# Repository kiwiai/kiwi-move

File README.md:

The Kiwi Move

These are the hardware design files for the Kiwi Move, developed by Kiwi Wearable Technologies Ltd.

These files have been made available online through a Creative Commons Attribution-ShareAlike 3.0 license. You are welcome to distribute, remix, and use these files for commercial purposes. If you do so, please attribute the original design to Kiwi Wearable Technologies Ltd. and all parties involved in developing to this point including Spark Devices in your schematic. All derivative works must be published under the same or a similar license. The design is built off of a number of open source projects including the Spark Core (https://github.com/spark/core)

Development of the Kiwi Move began in May 2013 in Toronto, Canada after the founding team participated in a local computer competition. The Kiwi Platform began its development in the spring of 2011 built on the basis of a number of sensorial and data acquisition devices. This initial release of hardware design files are for those in the GitHub and open-source community to make the most of for wearable technology devices.

What Hardware Design Files are Included:

EAGLE — Schematic and board files for the Kiwi Move. 

GERBER Files - For making your own runs of the Kiwi Move.

Pin Mapping — Detailed pin mapping of the Kiwi Move and STM32, providing information about which pins are mapped to which peripherals.

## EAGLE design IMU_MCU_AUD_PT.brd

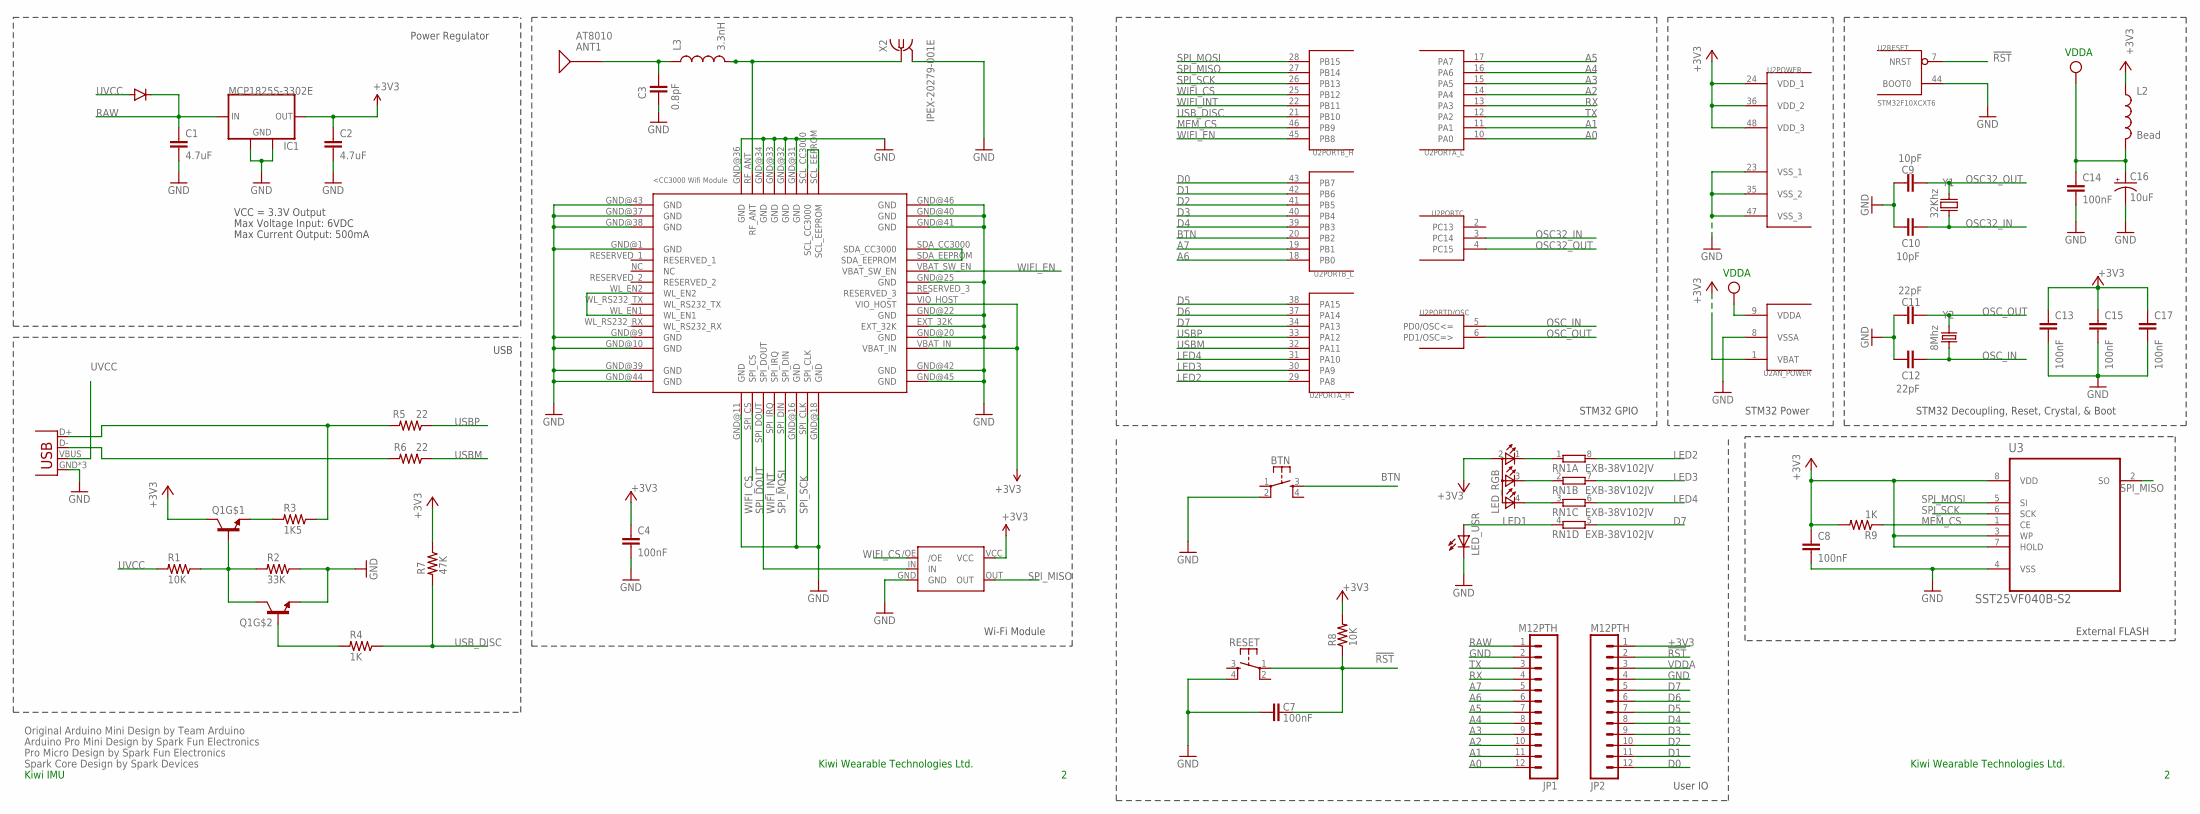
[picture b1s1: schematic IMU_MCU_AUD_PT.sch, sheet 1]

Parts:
ANT1: AT8010
B1: NL17SZ125SOT553; SOT-553
BTN: KMR211GLFS; TACTILE_SWITCH_SMD
C1, C2: 4.7uF; C0603
C3: 0.8pF; C0603
C4, C7, C8, C13, C14, C15, C17: 100nF; C0603
C9, C10: 10pF; C0603
C11, C12: 22pF; C0603
C16: 10uF; EIA3216
IC1: MCP1825S-3302E; SOT223
JP1, JP2: M12PTH; 1X12-SMALL-PADS
L2: Bead; 0603
L3: 3.3nH; 0603
LED_RGB: TOPLED-3PLCC; P-LCC-4-3
LED_USR: LED0603; LED-0603
Q1: MMDT3904; SOT363
R1, R8: 10K; R0603
R2: 33K; R0603
R3: 1K5; R0603
R4, R9: 1K; R0603
R5, R6: 22; R0603
R7: 47K; R0603
RESET: KMR211GLFS; TACTILE_SWITCH_SMD
RN1: EXB-38V102JV; EXB38V
U1: CC3000
U2: STM32F10XCXT6; TQFP48
U3: SST25VF040B-S2; SOIC127P790X216-8N
U$3: DIODE; DIODE-DO-220AA(SMP)
X1: USB-MICROB; USB-MICROB-SLOT-HOLE
X2: IPEX-20279-001E
Y1: 32Khz; FC135
Y2: 8Mhz; CRYSTAL-SMD-5X3

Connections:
3.3V: B1.VCC
!RST: C7.2, JP2.2, R8.1, RESET.1, U2.7 (NRST)
+3V3: C2.1, C4.1, C8.1, C13.1, C15.1, C17.1, IC1.3 (OUT), JP2.1, L2.1, LED_RGB.2 (A2), Q1.3 (C), R7.1, R8.2, R9.2, U1.VBAT_IN, U1.VIO_HOST, U2.1 (VBAT), U2.24 (VDD_1), U2.36 (VDD_2), U2.48 (VDD_3), U3.3 (WP), U3.7 (HOLD), U3.8 (VDD); also elsewhere on the board
A0: JP1.12, U2.10 (PA0); also elsewhere on the board
A1: JP1.11, U2.11 (PA1); also elsewhere on the board
A2: JP1.10, U2.14 (PA4)
A3: JP1.9, U2.15 (PA5)
A4: JP1.8, U2.16 (PA6)
A5: JP1.7, U2.17 (PA7)
A6: JP1.6, U2.18 (PB0); also elsewhere on the board
A7: JP1.5, U2.19 (PB1)
BTN: BTN.3, U2.20 (PB2)
D0: JP2.12, U2.43 (PB7); also elsewhere on the board
D1: JP2.11, U2.42 (PB6); also elsewhere on the board
D2: JP2.10, U2.41 (PB5)
D3: JP2.9, U2.40 (PB4); also elsewhere on the board
D4: JP2.8, U2.39 (PB3); also elsewhere on the board
D5: JP2.7, U2.38 (PA15); also elsewhere on the board
D6: JP2.6, U2.37 (PA14); also elsewhere on the board
D7: JP2.5, RN1.5 (2), U2.34 (PA13)
GND: B1.GND, BTN.2, C1.2, C2.2, C3.1, C4.2, C7.1, C8.2, C9.2, C10.2, C11.2, C12.2, C13.2, C14.2, C15.2, C16.C (-), C17.2, IC1.2 (GND), IC1.4 (GND), JP1.2, JP2.4, LED_USR.C, Q1.1 (E), R2.1, RESET.4, U1.EXT_32K, U1.GND@1 (GND), U1.GND@9 (GND), U1.GND@10 (GND), U1.GND@11 (GND), U1.GND@16 (GND), U1.GND@18 (GND), U1.GND@20 (GND), U1.GND@22 (GND), U1.GND@25 (GND), U1.GND@31 (GND), U1.GND@32 (GND), U1.GND@33 (GND), U1.GND@34 (GND), U1.GND@36 (GND), U1.GND@37 (GND), U1.GND@38 (GND), U1.GND@39 (GND), U1.GND@40 (GND), U1.GND@41 (GND), U1.GND@42 (GND), U1.GND@43 (GND), U1.GND@44 (GND), U1.GND@45 (GND), U1.GND@46 (GND), U2.8 (VSSA), U2.23 (VSS_1), U2.35 (VSS_2), U2.44 (BOOT0), U2.47 (VSS_3), U3.4 (VSS), X1.GND, X1.MT1 (GND), X1.MT2 (GND), X2.2@1 (GND), X2.2@2 (GND); also elsewhere on the board
LED1: LED_USR.A, RN1.4 (1)
LED2: RN1.8 (2), U2.29 (PA8)
LED3: RN1.7 (2), U2.30 (PA9)
LED4: RN1.6 (2), U2.31 (PA10)
MEM_CS: R9.1, U2.46 (PB9), U3.1 (CE)
unnamed: R3.1, R5.2, X1.D+
unnamed: ANT1.SIG, C3.2, L3.1
unnamed: L3.2, U1.RF_ANT, X2.1
unnamed: R6.2, X1.D-
unnamed: U1.SCL_CC3000, U1.SCL_EEPROM
unnamed: Q1.2 (B), R4.2
unnamed: U1.WL_EN1, U1.WL_EN2
unnamed: LED_RGB.1 (CRED), RN1.1
unnamed: LED_RGB.3 (CBLUE), RN1.2 (1)
unnamed: Q1.5 (B), Q1.6 (C), R1.1, R2.2
unnamed: LED_RGB.4 (CGREEN), RN1.3 (1)
unnamed: U1.SDA_CC3000, U1.SDA_EEPROM
unnamed: Q1.4 (E), R3.2
OSC32_IN: C10.1, U2.3 (PC14), Y1.X1 (1)
OSC32_OUT: C9.1, U2.4 (PC15), Y1.X2 (2)
OSC_IN: C12.1, U2.5 (PD0/OSC<=), Y2.1
OSC_OUT: C11.1, U2.6 (PD1/OSC=>), Y2.3 (2)
RAW: C1.1, IC1.1 (IN), JP1.1, U$3.CATHODE
RX: JP1.4, U2.13 (PA3)
SPI_DOUT: B1.IN, U1.SPI_DOUT
SPI_MISO: B1.OUT, U2.27 (PB14), U3.2 (SO)
SPI_MOSI: U1.SPI_DIN, U2.28 (PB15), U3.5 (SI)
SPI_SCK: U1.SPI_CLK, U2.26 (PB13), U3.6 (SCK)
TX: JP1.3, U2.12 (PA2)
USBM: R6.1, U2.32 (PA11)
USBP: R5.1, U2.33 (PA12)
USB_DISC: R4.1, R7.2, U2.21 (PB10)
UVCC: R1.2, U$3.ANODE, X1.VBUS
VDDA: C14.1, C16.A (+), JP2.3, L2.2, U2.9 (VDDA)
WIFI_CS: B1./OE, U1.SPI_CS, U2.25 (PB12)
WIFI_EN: U1.VBAT_SW_EN, U2.45 (PB8)
WIFI_INT: U1.SPI_IRQ, U2.22 (PB11)

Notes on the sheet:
Original Arduino Mini Design by Team Arduino
Arduino Pro Mini Design by Spark Fun Electronics
Max Voltage Input: 6VDC
Max Current Output: 500mA
Power Regulator
VCC = 3.3V Output
Pro Micro Design by Spark Fun Electronics
Spark Core Design by Spark Devices
STM32 Decoupling, Reset, Crystal, & Boot
STM32 GPIO
STM32 Power
External FLASH
User IO
USB
Wi-Fi Module
VDDA
Kiwi IMU
Kiwi Wearable Technologies Ltd.

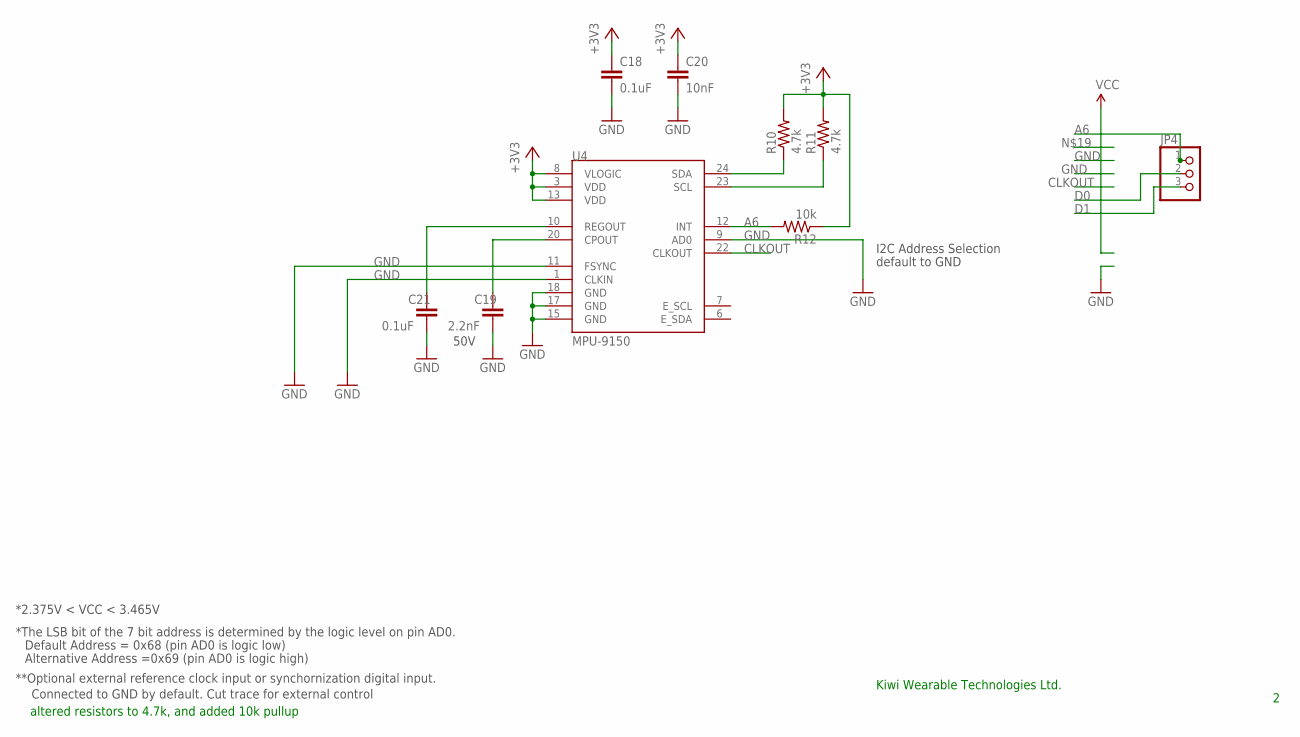
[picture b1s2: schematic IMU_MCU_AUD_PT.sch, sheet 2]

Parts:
C18, C21: 0.1uF; 0402-CAP
C19: 2.2nF; 0402-CAP
C20: 10nF; 0402-CAP
JP4: PINHD-1X3; 1X03
R10, R11: 4.7k; 0402-RES
R12: 10k; 0402-RES
U4: MPU-9150; QFN-24-NP

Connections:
+3V3: C18.1, C20.1, R10.2, R11.2, R12.1, U4.3 (VDD), U4.8 (VLOGIC), U4.13 (VDD); also elsewhere on the board
A6: JP4.1, R12.2, U4.12 (INT); also elsewhere on the board
CLKOUT: U4.22 (CLKOUT)
D0: JP4.2, R10.1, U4.24 (SDA); also elsewhere on the board
D1: JP4.3, R11.1, U4.23 (SCL); also elsewhere on the board
GND: C18.2, C19.2, C20.2, C21.2, U4.1 (CLKIN), U4.9 (AD0), U4.11 (FSYNC), U4.15 (GND), U4.17 (GND), U4.18 (GND); also elsewhere on the board
unnamed: C19.1, U4.20 (CPOUT)
unnamed: C21.1, U4.10 (REGOUT)

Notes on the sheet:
50V
I2C Address Selection
**Optional external reference clock input or synchornization digital input.
Connected to GND by default. Cut trace for external control
Default Address = 0x68 (pin AD0 is logic low)
Alternative Address =0x69 (pin AD0 is logic high)
*The LSB bit of the 7 bit address is determined by the logic level on pin AD0.
default to GND
*2.375V < VCC < 3.465V
altered resistors to 4.7k, and added 10k pullup
Kiwi Wearable Technologies Ltd.

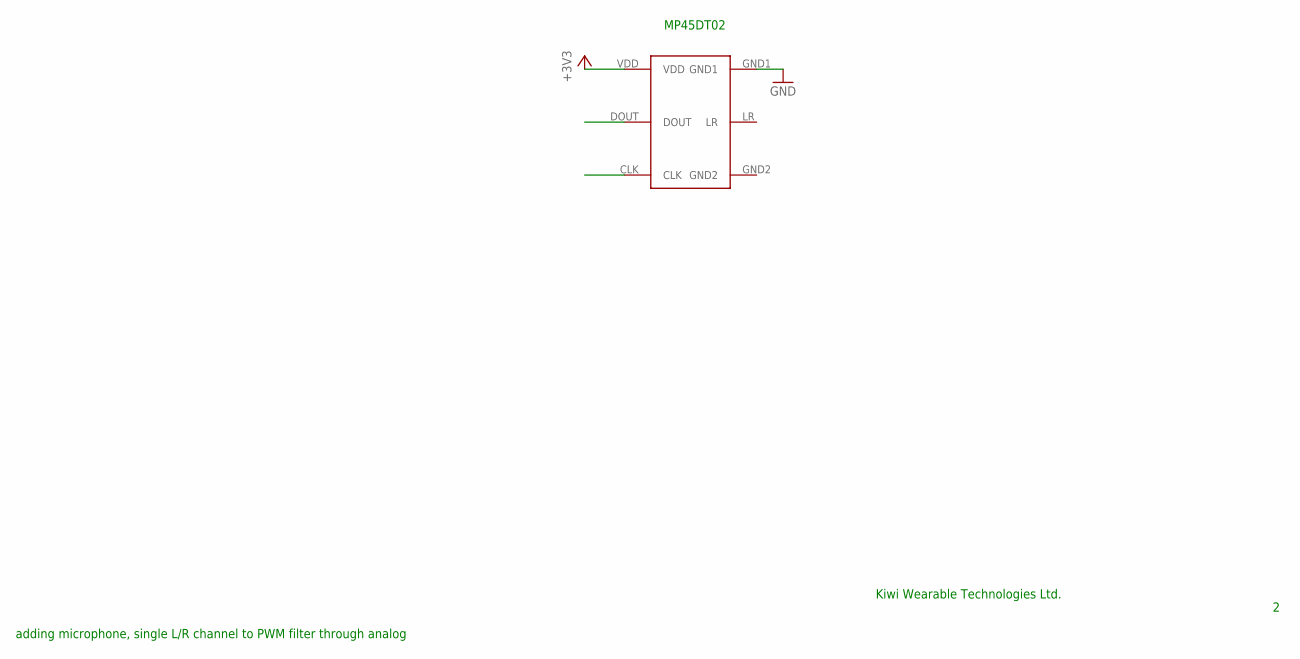
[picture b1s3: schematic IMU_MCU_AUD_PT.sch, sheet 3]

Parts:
M1: MP45DT02; HLGA

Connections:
+3V3: M1.VDD; also elsewhere on the board
A0: M1.CLK; also elsewhere on the board
A1: M1.DOUT; also elsewhere on the board
GND: M1.GND1; also elsewhere on the board

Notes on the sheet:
Kiwi Wearable Technologies Ltd.
MP45DT02
adding microphone, single L/R channel to PWM filter through analog

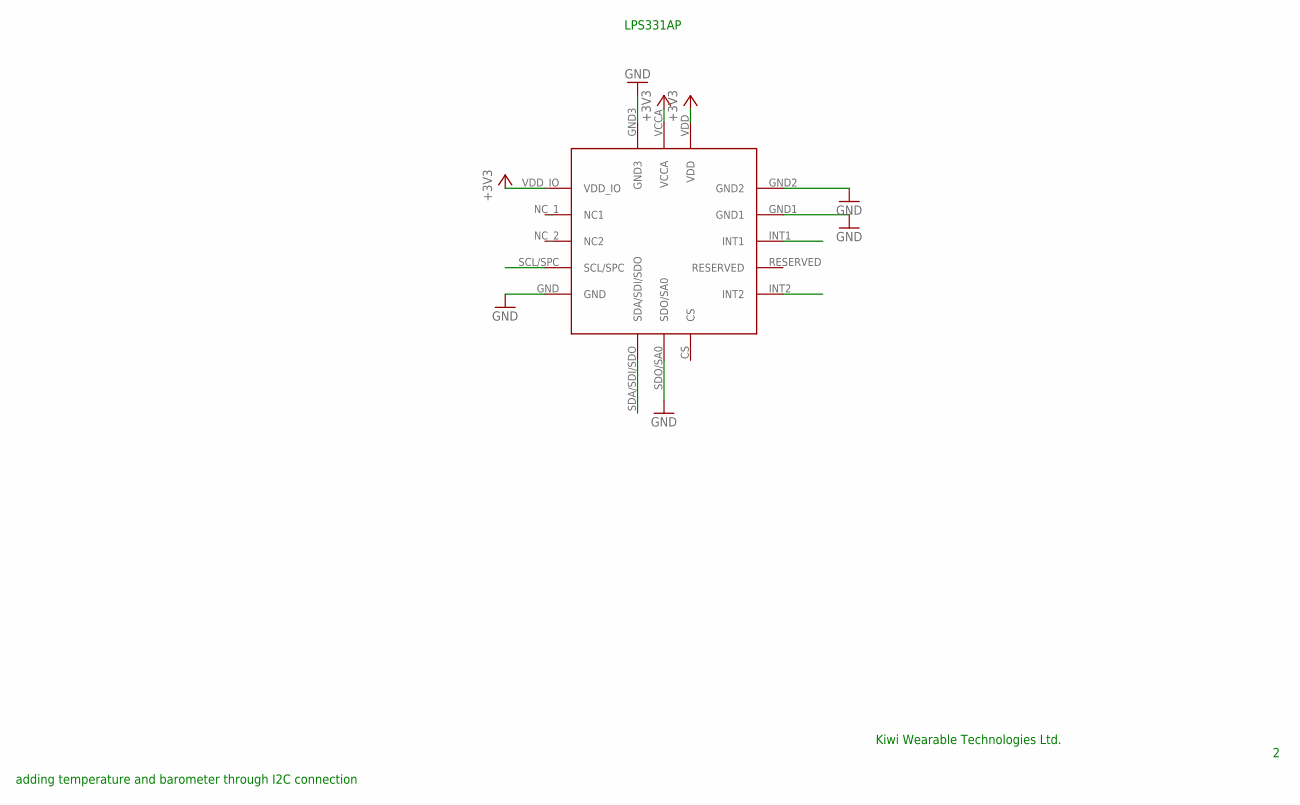
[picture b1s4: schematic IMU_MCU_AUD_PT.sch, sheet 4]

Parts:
P1: LPS331AP; HCLGA

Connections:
+3V3: P1.VCCA, P1.VDD, P1.VDD_IO; also elsewhere on the board
D3: P1.INT1; also elsewhere on the board
D4: P1.INT2; also elsewhere on the board
D5: P1.SCL/SPC; also elsewhere on the board
D6: P1.SDA/SDI/SDO; also elsewhere on the board
GND: P1.GND, P1.GND1, P1.GND2, P1.GND3, P1.SDO/SA0; also elsewhere on the board

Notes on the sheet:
Kiwi Wearable Technologies Ltd.
LPS331AP
adding temperature and barometer through I2C connection

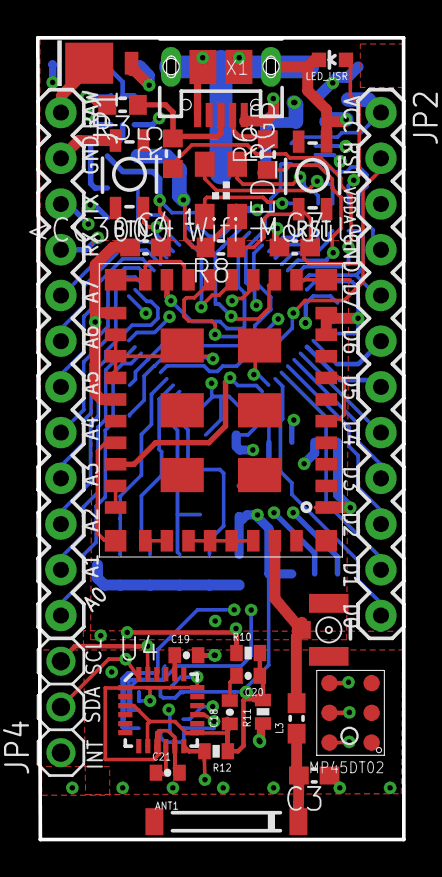
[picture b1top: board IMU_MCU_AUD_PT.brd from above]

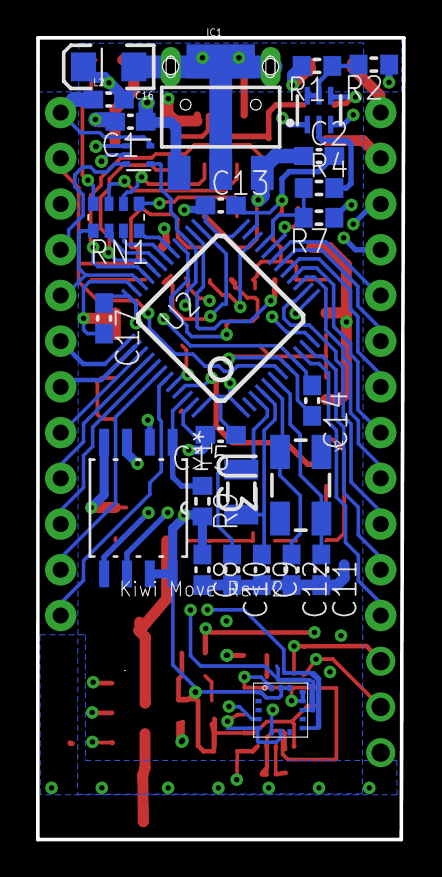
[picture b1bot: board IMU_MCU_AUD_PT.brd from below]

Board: 4 copper layers, 20.3 x 44.5 mm, 56 parts (27 on the bottom side), 59 nets.

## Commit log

2013-11-14 Get your move on with opensource!
2013-11-14 fixing boarding and schematic layout

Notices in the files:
parts and their libraries:
SparkFun-Passives: Licensing: CC v3.0 Share-Alike You are welcome to use this library for commercial purposes.
SparkFun-Aesthetics: Released under the Creative Commons
SparkFun-Aesthetics: http://creativecommons.org/licenses/by-sa/3.0
